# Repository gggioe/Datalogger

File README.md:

# Datalogger
Esp32 voltage/current logger

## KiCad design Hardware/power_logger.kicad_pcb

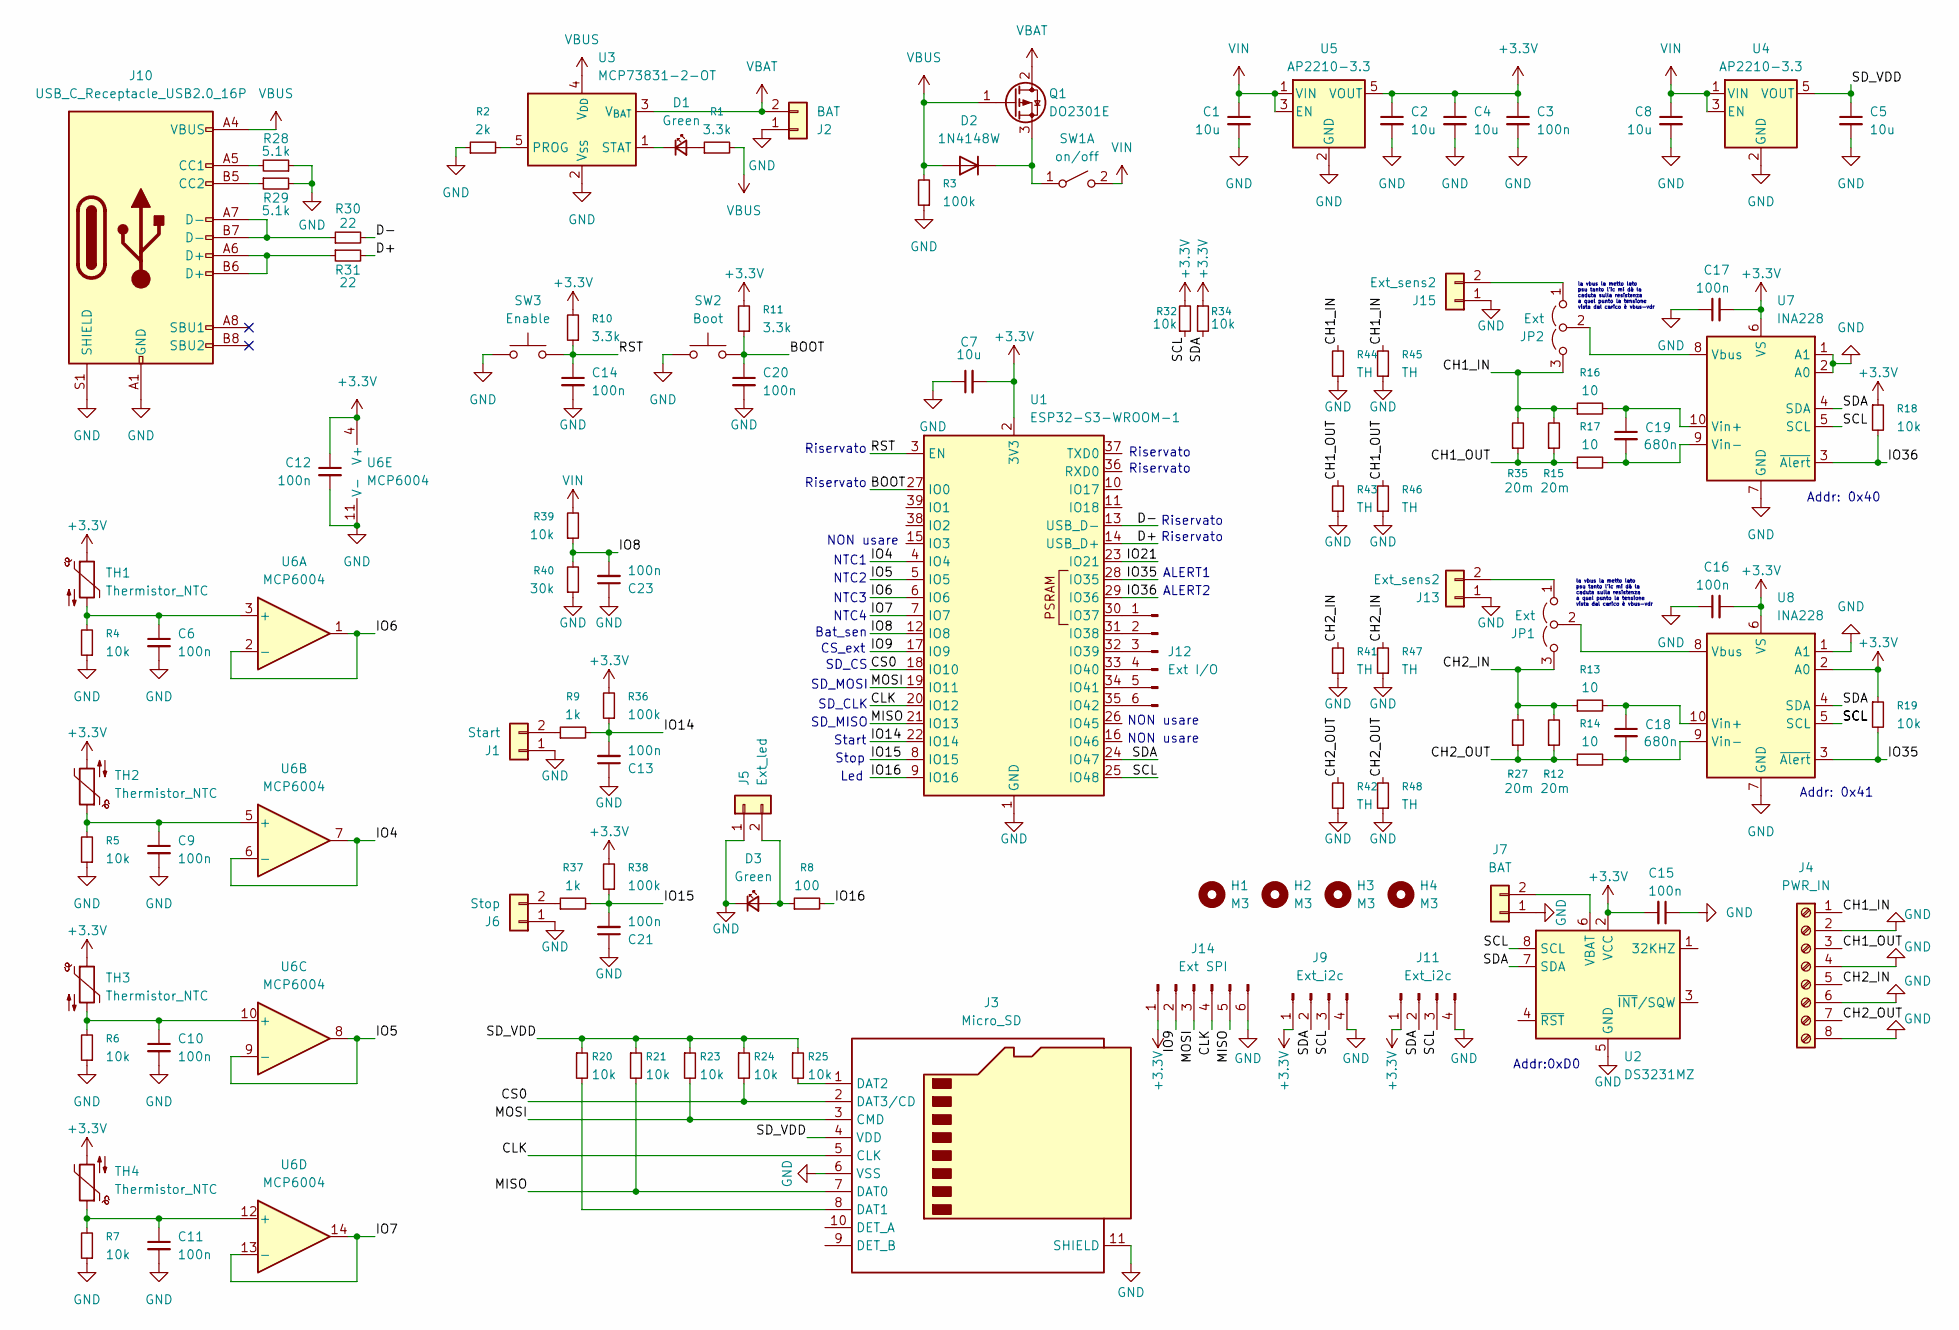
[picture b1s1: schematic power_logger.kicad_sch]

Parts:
C1, C2, C4, C5, C7, C8: 10u; C_0603_1608Metric_Pad1.08x0.95mm_HandSolder
C3, C6, C9, C10, C11, C12, C13, C14, C15, C16, C17, C20, C21, C23: 100n; C_0603_1608Metric_Pad1.08x0.95mm_HandSolder
C18, C19: 680n; C_0603_1608Metric_Pad1.08x0.95mm_HandSolder
D1, D3: Green; LED_0603_1608Metric_Pad1.05x0.95mm_HandSolder
D2: 1N4148W; D_SOD-123
H1, H2, H3, H4: M3; MountingHole_3.2mm_M3
J1: Start; JST_PH_B2B-PH-K_1x02_P2.00mm_Vertical
J2, J7: BAT; JST_PH_B2B-PH-K_1x02_P2.00mm_Vertical
J3: Micro_SD; microSD_HC_Molex_104031-0811_Handsolder
J4: PWR_IN; TerminalBlock_MaiXu_MX126-5.0-08P_1x08_P5.00mm
J5: Ext_led; JST_PH_B2B-PH-K_1x02_P2.00mm_Vertical
J6: Stop; JST_PH_B2B-PH-K_1x02_P2.00mm_Vertical
J9, J11: Ext_i2c; JST_PH_B4B-PH-K_1x04_P2.00mm_Vertical
J10: USB_C_Receptacle_USB2.0_16P; USB_C_Receptacle_G-Switch_GT-USB-7010ASV
J12: Ext I/O; JST_PH_B6B-PH-K_1x06_P2.00mm_Vertical
J13, J15: Ext_sens2; JST_PH_B2B-PH-K_1x02_P2.00mm_Vertical
J14: Ext SPI; JST_PH_B6B-PH-K_1x06_P2.00mm_Vertical
JP1, JP2: Ext; SolderJumper-3_P1.3mm_Open_RoundedPad1.0x1.5mm_NumberLabels
Q1: DO2301E; TSOT-23_HandSoldering
R1, R10, R11: 3.3k; R_0603_1608Metric_Pad0.98x0.95mm_HandSolder
R2: 2k; R_0603_1608Metric_Pad0.98x0.95mm_HandSolder
R3, R36, R38: 100k; R_0603_1608Metric_Pad0.98x0.95mm_HandSolder
R4, R5, R6, R7, R18, R19, R20, R21, R23, R24, R25, R32, R34, R39: 10k; R_0603_1608Metric_Pad0.98x0.95mm_HandSolder
R8: 100; R_0603_1608Metric_Pad0.98x0.95mm_HandSolder
R9, R37: 1k; R_0603_1608Metric_Pad0.98x0.95mm_HandSolder
R12, R15, R27, R35: 20m; RESC6772X124N
R13, R14, R16, R17: 10; R_0603_1608Metric_Pad0.98x0.95mm_HandSolder
R28, R29: 5.1k; R_0603_1608Metric_Pad0.98x0.95mm_HandSolder
R30, R31: 22; R_0603_1608Metric_Pad0.98x0.95mm_HandSolder
R40: 30k; R_0603_1608Metric_Pad0.98x0.95mm_HandSolder
R41, R42, R43, R44, R45, R46, R47, R48: TH; R_2512_6332Metric_Pad1.40x3.35mm_HandSolder
SW1: on/off; JST_PH_B2B-PH-K_1x02_P2.00mm_Vertical
SW2: Boot; SW_SPST_SKQG_WithStem
SW3: Enable; SW_SPST_SKQG_WithStem
TH1, TH2, TH3, TH4: Thermistor_NTC; JST_PH_B2B-PH-K_1x02_P2.00mm_Vertical
U1: ESP32-S3-WROOM-1
U2: DS3231MZ; SOIC-8_3.9x4.9mm_P1.27mm
U3: MCP73831-2-OT; SOT-23-5
U4, U5: AP2210-3.3; SOT-23-5
U6: MCP6004; SOIC-14_3.9x8.7mm_P1.27mm
U7, U8: INA228; VSSOP-10_3x3mm_P0.5mm

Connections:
+3.3V: C2.1, C3.1, C4.1, C7.2, C12.1, C15.2, C16.2, C17.2, J9.1, J11.1, J14.1, R10.2, R11.2, R18.1, R19.1, R32.2, R34.1, R36.2, R38.2, TH1.1, TH2.2, TH3.1, TH4.2, U1.2 (3V3), U2.2 (VCC), U5.5 (VOUT), U6.4 (V+), U7.6 (VS), U8.2 (A0), U8.6 (VS); also elsewhere on the board
/BOOT: C20.1, R11.1, SW2.2, U1.27 (IO0)
/CH1_IN: J4.1, JP2.3 (B), R15.2, R16.1, R35.2, R44.2, R45.2
/CH1_OUT: J4.3, R15.1, R17.1, R35.1, R43.2, R46.2
/CH2_IN: J4.5, JP1.3 (B), R12.2, R13.1, R27.2, R41.2, R47.2
/CH2_OUT: J4.7, R12.1, R14.1, R27.1, R42.2, R48.2
/CLK: J3.5 (CLK), J14.4, U1.20 (IO12); also elsewhere on the board
/CS0: J3.2 (DAT3/CD), R24.2, U1.18 (IO10)
/D+: R31.2, U1.14 (USB_D+)
/D-: R30.2, U1.13 (USB_D-)
/IO4: U1.4 (IO4), U6.6 (-), U6.7
/IO5: U1.5 (IO5), U6.8, U6.9 (-)
/IO6: U1.6 (IO6), U6.1, U6.2 (-)
/IO7: U1.7 (IO7), U6.13 (-), U6.14
/IO8: C23.2, R39.1, R40.2, U1.12 (IO8)
/IO9: J14.2, U1.17 (IO9)
/IO14: C13.2, R9.2, R36.1, U1.22 (IO14)
/IO15: C21.2, R37.2, R38.1, U1.8 (IO15)
/IO16: R8.2, U1.9 (IO16)
/IO21: U1.23 (IO21)
/IO35: R19.2, U1.28 (IO35), U8.3 (~Alert)
/IO36: R18.2, U1.29 (IO36), U7.3 (~Alert)
/MISO: J3.7 (DAT0), J14.5, R21.2, U1.21 (IO13)
/MOSI: J3.3 (CMD), J14.3, R23.2, U1.19 (IO11)
/RST: C14.1, R10.1, SW3.2, U1.3 (EN)
/SCL: J9.3, J11.3, R32.1, U1.25 (IO48), U2.8 (SCL), U7.5 (SCL), U8.5 (SCL)
/SDA: J9.2, J11.2, R34.2, U1.24 (IO47), U2.7 (SDA), U7.4 (SDA), U8.4 (SDA)
/SD_VDD: C5.1, J3.4 (VDD), R20.1, R21.1, R23.1, R24.1, R25.1, U4.5 (VOUT); also elsewhere on the board
GND: C1.2, C2.2, C3.2, C4.2, C5.2, C6.2, C7.1, C8.2, C9.2, C10.2, C11.2, C12.2, C13.1, C14.2, C15.1, C16.1, C17.1, C20.2, C21.1, C23.1, D3.1 (K), J1.1, J2.1, J3.6 (VSS), J3.11 (SHIELD), J4.2, J4.4, J4.6, J4.8, J5.1, J6.1, J7.1, J9.4, J10.A1 (GND), J10.A12 (GND), J10.B1 (GND), J10.B12 (GND), J10.S1 (SHIELD), J11.4, J13.1, J14.6, J15.1, R2.1, R3.1, R4.1, R5.1, R6.1, R7.1, R28.1, R29.2, R40.1, R41.1, R42.1, R43.1, R44.1, R45.1, R46.1, R47.1, R48.1, SW2.1, SW3.1, U1.1 (GND), U1.40 (GND), U1.41 (GND), U2.5 (GND), U3.2 (V_{SS}), U4.2 (GND), U5.2 (GND), U6.11 (V-), U7.1 (A1), U7.2 (A0), U7.7 (GND), U8.1 (A1), U8.7 (GND); also elsewhere on the board
unnamed: D1.2 (A), R1.1
unnamed: D1.1 (K), U3.1 (STAT)
unnamed: D2.1 (K), Q1.3 (S), SW1.1 (A)
unnamed: D3.2 (A), J5.2, R8.1
unnamed: J1.2, R9.1
unnamed: J3.8 (DAT1), R20.2
unnamed: J3.1 (DAT2), R25.2
unnamed 36: J3.10 (DET_A); also elsewhere on the board
unnamed 37: J3.9 (DET_B); also elsewhere on the board
unnamed: J6.2, R37.1
unnamed: J7.2, U2.6 (VBAT)
unnamed: J10.A5 (CC1), R28.2
unnamed: J10.B5 (CC2), R29.1
unnamed: J10.A6 (D+), J10.B6 (D+), R31.1
unnamed: J10.A7 (D-), J10.B7 (D-), R30.1
unnamed: J12.1, U1.30 (IO37)
unnamed: J12.2, U1.31 (IO38)
unnamed: J12.3, U1.32 (IO39)
unnamed: J12.4, U1.33 (IO40)
unnamed: J12.5, U1.34 (IO41)
unnamed: J12.6, U1.35 (IO42)
unnamed: J13.2, JP1.1 (A)
unnamed: J15.2, JP2.1 (A)
unnamed: JP1.2 (C), U8.8 (Vbus)
unnamed: JP2.2 (C), U7.8 (Vbus)
unnamed: R2.2, U3.5 (PROG)
unnamed: C6.1, R4.2, TH1.2, U6.3 (+)
unnamed: C9.1, R5.2, TH2.1, U6.5 (+)
unnamed: C10.1, R6.2, TH3.2, U6.10 (+)
unnamed: C11.1, R7.2, TH4.1, U6.12 (+)
unnamed: C19.1, R16.2, U7.10 (Vin+)
unnamed: C19.2, R17.2, U7.9 (Vin-)
unnamed: C18.1, R13.2, U8.10 (Vin+)
unnamed: C18.2, R14.2, U8.9 (Vin-)
VBAT: J2.2, Q1.2 (D), U3.3 (V_{BAT})
VBUS: D2.2 (A), J10.A4 (VBUS), J10.A9 (VBUS), J10.B4 (VBUS), J10.B9 (VBUS), Q1.1 (G), R1.2, R3.2, U3.4 (V_{DD})
VIN: C1.1, C8.1, R39.2, SW1.2 (B), U4.1 (VIN), U4.3 (EN), U5.1 (VIN), U5.3 (EN)

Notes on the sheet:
SD_CLK
NTC2
NON usare
Riservato
SD_MOSI
Led
la vbus la metto lato psu tanto l'ic mi dà la caduta sulla resistenza a quel punto la tensione vista dal carico è vbus-vdr
Addr: 0x40
NTC1
Addr:0xD0
ALERT2
Start
ALERT1
NTC4
SD_CS
Bat_sen
CS_ext
Addr: 0x41
SD_MISO
NTC3
Stop

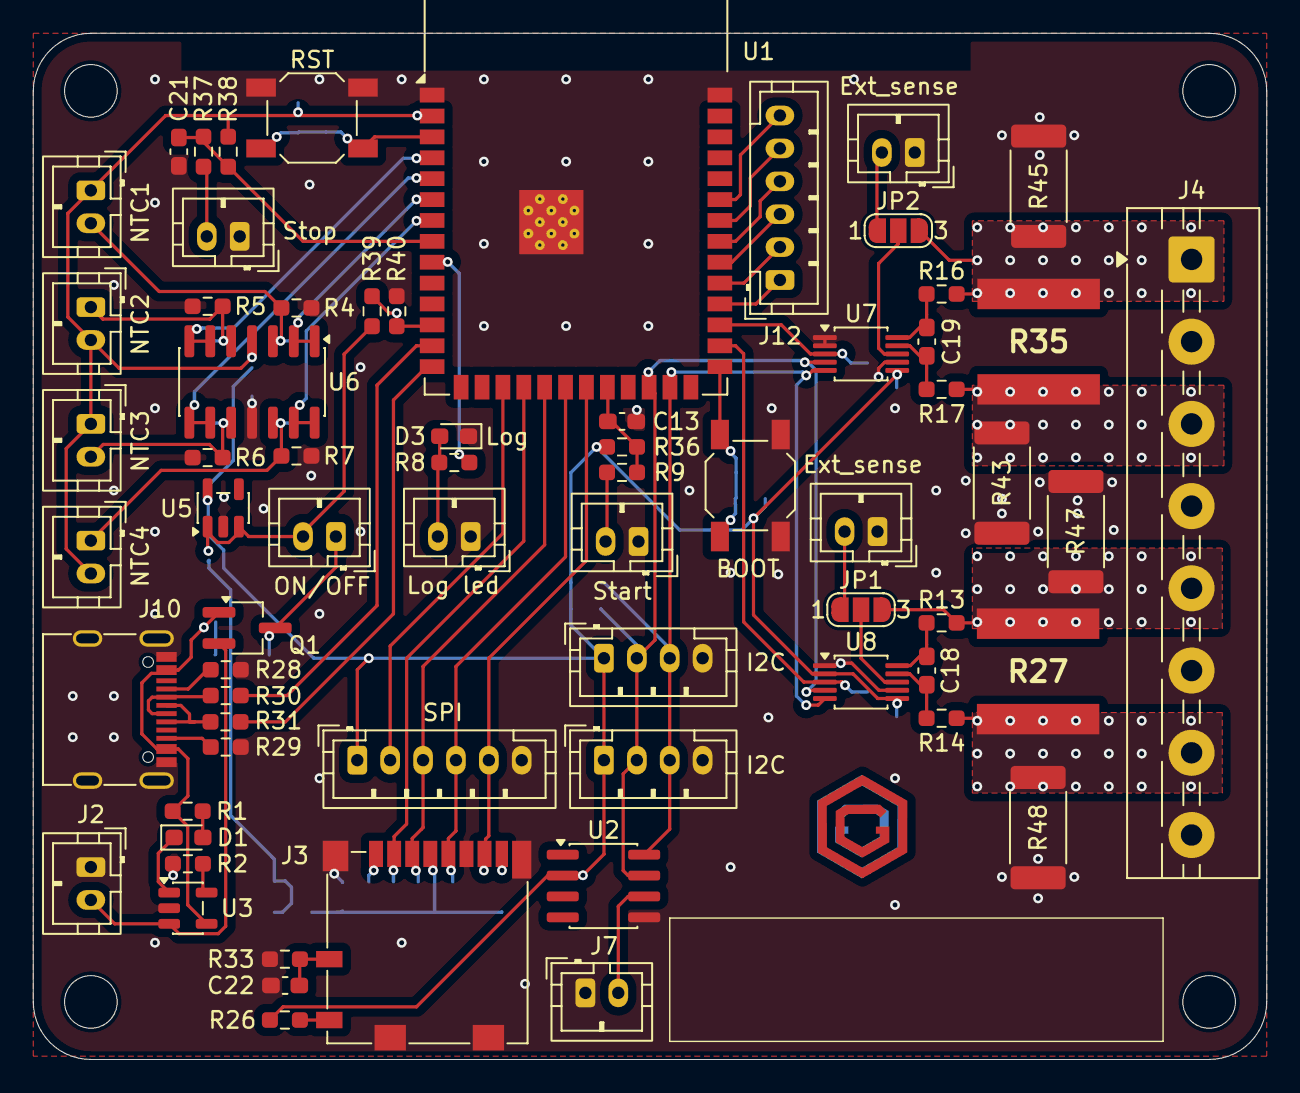
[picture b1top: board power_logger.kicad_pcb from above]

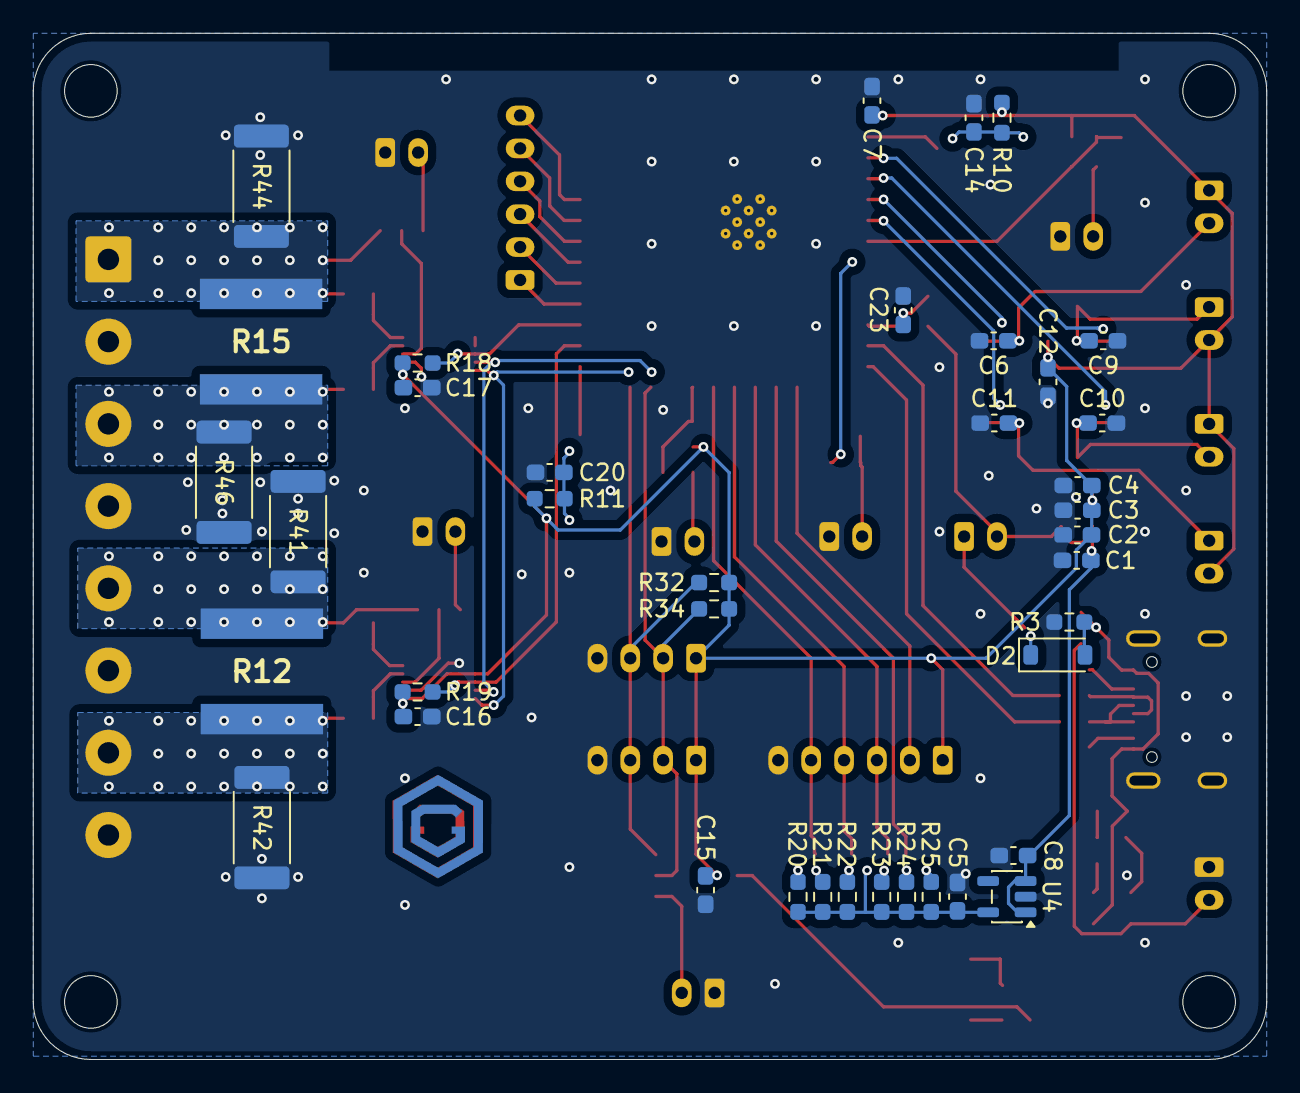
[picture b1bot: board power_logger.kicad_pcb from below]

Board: 2 copper layers, 75.0 x 62.4 mm, 110 parts (39 on the bottom side), 65 nets.

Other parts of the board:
C22: 1u; C_0603_1608Metric_Pad1.08x0.95mm_HandSolder
R22, R33: 10k; R_0603_1608Metric_Pad0.98x0.95mm_HandSolder
R26: 1k; R_0603_1608Metric_Pad0.98x0.95mm_HandSolder

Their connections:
+3.3V: R26.1; also elsewhere on the board
/CLK: R22.2; also elsewhere on the board
/SD_VDD: R22.1; also elsewhere on the board
GND: C22.2, R33.2; also elsewhere on the board
unnamed 36: R26.2; also elsewhere on the board
unnamed 37: C22.1, R33.1; also elsewhere on the board

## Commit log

2026-03-30 Add files
2026-04-03 minor updates
2026-04-05 added influxdb
2026-04-15 added timestamp
2026-04-18 removed influxdb
2026-04-18 minor cleanup
2026-04-21 Added hardware rev1.0
2026-04-21 menu dev
2026-04-21 added menu switch
2026-04-21 improved menu
2026-04-22 dev test corda
2026-04-22 dev update
2026-04-23 minor fix
2026-05-01 removed load cell support
